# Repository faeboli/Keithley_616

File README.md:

# Keithley_616
Modification to Keithley 616 input buffer:
My keithkey 616 had the input mosfet Q101 broken,
I lately was not happy with it's performance, current leakage was 0.3pA, zero was drifty.
So my idea was to replace the input circuitry with a modern opamp, reading around the
perfect candidate was the LMC6081, a low leakage mosfet opamp.
In order to replace the input buffer, the zero circuit need to be reimplemented.
I have posted some pics in this eevblog thread:

https://www.eevblog.com/forum/repair/keithley-616-electrometer-input-stage-replacement/

The schematic is very simple, this part (PC361 in the box below):

will be replaced by this, C5 R6 need to be tuned manually:

I have also created a PCB project:

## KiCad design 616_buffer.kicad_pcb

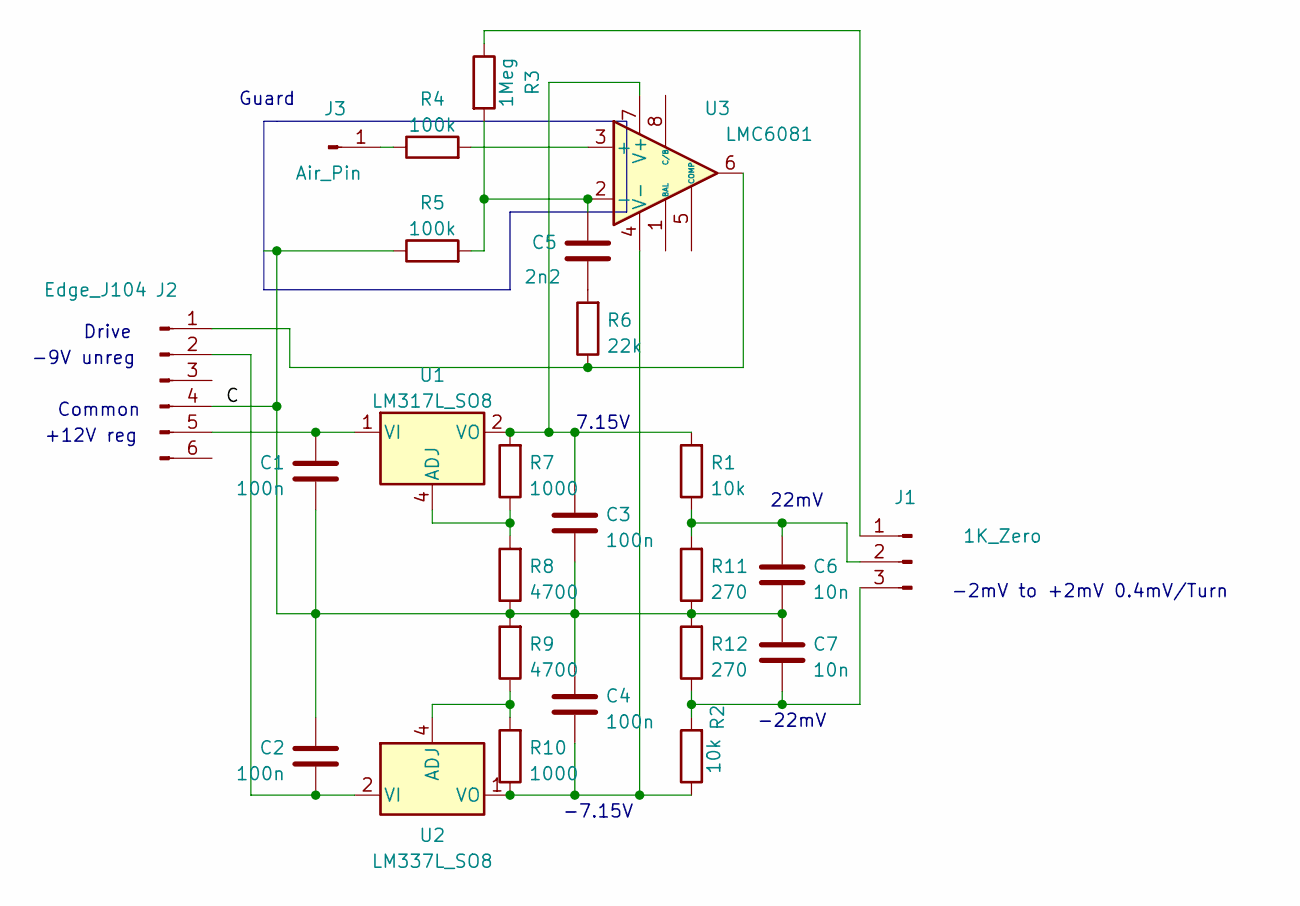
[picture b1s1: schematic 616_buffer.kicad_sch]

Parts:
C1, C2, C3, C4: 100n; C_0805_2012Metric
C5: 2n2; C_Rect_L10.0mm_W2.5mm_P7.50mm_MKS4
C6, C7: 10n; C_0805_2012Metric
J1: 1K_Zero; PinHeader_1x03_P2.54mm_Vertical
J2: Edge_J104; Hirose_DF63-6P-3.96DSA_1x06_P3.96mm_Vertical
J3: Air_Pin; TestPoint_Pad_D2.0mm
R1, R2: 10k; R_0805_2012Metric
R3: 1Meg; R_0805_2012Metric
R4, R5: 100k; R_0805_2012Metric
R6: 22k; R_0805_2012Metric
R7, R10: 1000; R_0805_2012Metric
R8, R9: 4700; R_0805_2012Metric
R11, R12: 270; R_0805_2012Metric
U1: LM317L_SO8; SOIC-8_3.9x4.9mm_P1.27mm
U2: LM337L_SO8; SOIC-8_3.9x4.9mm_P1.27mm
U3: LMC6081; SOIC-8_3.9x4.9mm_P1.27mm

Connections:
/C: C1.1, C2.2, C3.1, C4.2, C6.1, C7.2, J2.4, R5.1, R8.1, R9.2, R11.1, R12.2
unnamed: C1.2, J2.5, U1.1 (VI)
unnamed: C2.1, J2.2, U2.2 (VI), U2.3 (VI), U2.6 (VI), U2.7 (VI)
unnamed: C3.2, R1.2, R7.2, U1.2 (VO), U1.3 (VO), U1.6 (VO), U1.7 (VO), U3.7 (V+)
unnamed: C4.1, R2.1, R10.1, U2.1 (VO), U3.4 (V-)
unnamed: C5.1, R6.2
unnamed: C5.2, R3.2, R5.2, U3.2 (-)
unnamed: C6.2, J1.2, R1.1, R11.2
unnamed: C7.1, J1.3, R2.2, R12.1
unnamed: J1.1, R3.1
unnamed: J2.1, R6.1, U3.6
unnamed: J3.1, R4.1
unnamed: R4.2, U3.3 (+)
unnamed: R7.1, R8.2, U1.4 (ADJ)
unnamed: R9.1, R10.2, U2.4 (ADJ)

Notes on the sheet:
-7.15V
Guard
Common
+12V reg
7.15V
-2mV to +2mV 0.4mV/Turn
22mV
-9V unreg
-22mV
Drive

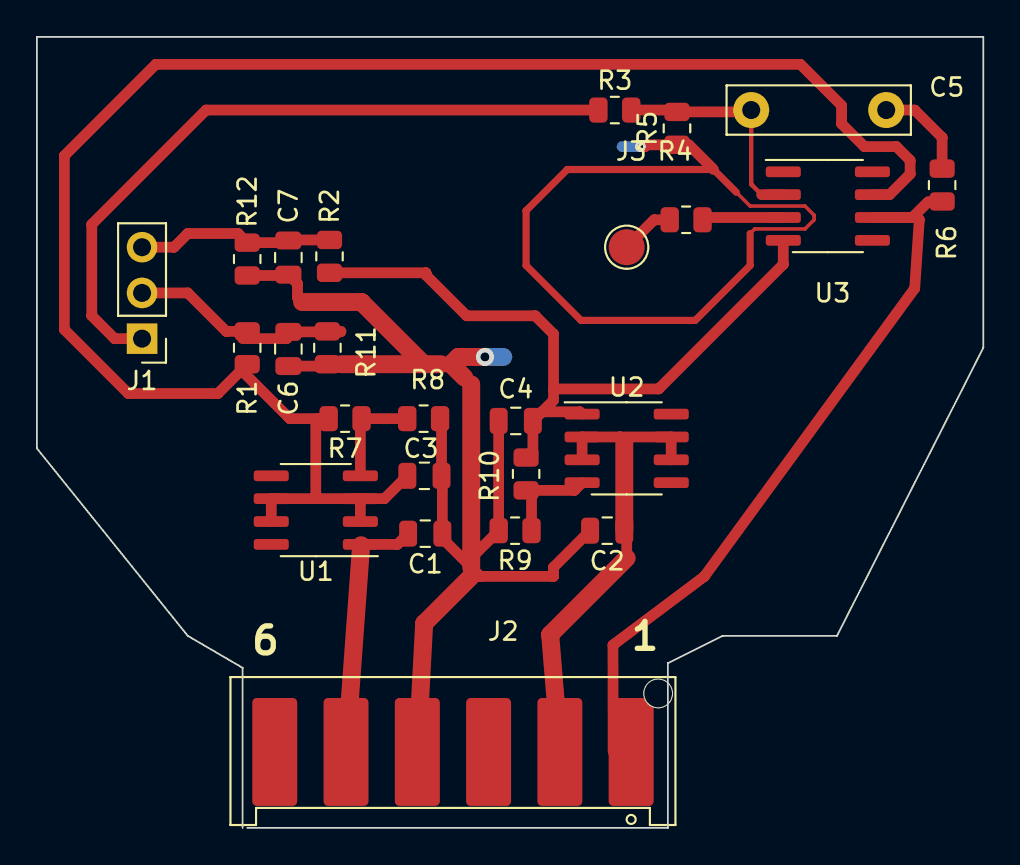
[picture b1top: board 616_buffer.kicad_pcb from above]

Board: 2 copper layers, 52.6 x 43.9 mm, 25 parts (0 on the bottom side), 15 nets.

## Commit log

2023-03-20 Fixed zero connector pinout
2023-03-20 Updated gerbers with correct zero connector pinout
2023-04-06 Fixed edge connector spacing
2023-04-06 removed old directory
2023-04-30 Update schematic
